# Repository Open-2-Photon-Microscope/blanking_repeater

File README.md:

# blanking_repeater
an electronic circuit to distribute blanking signal (or any type of ttl signal) to multiple outputs

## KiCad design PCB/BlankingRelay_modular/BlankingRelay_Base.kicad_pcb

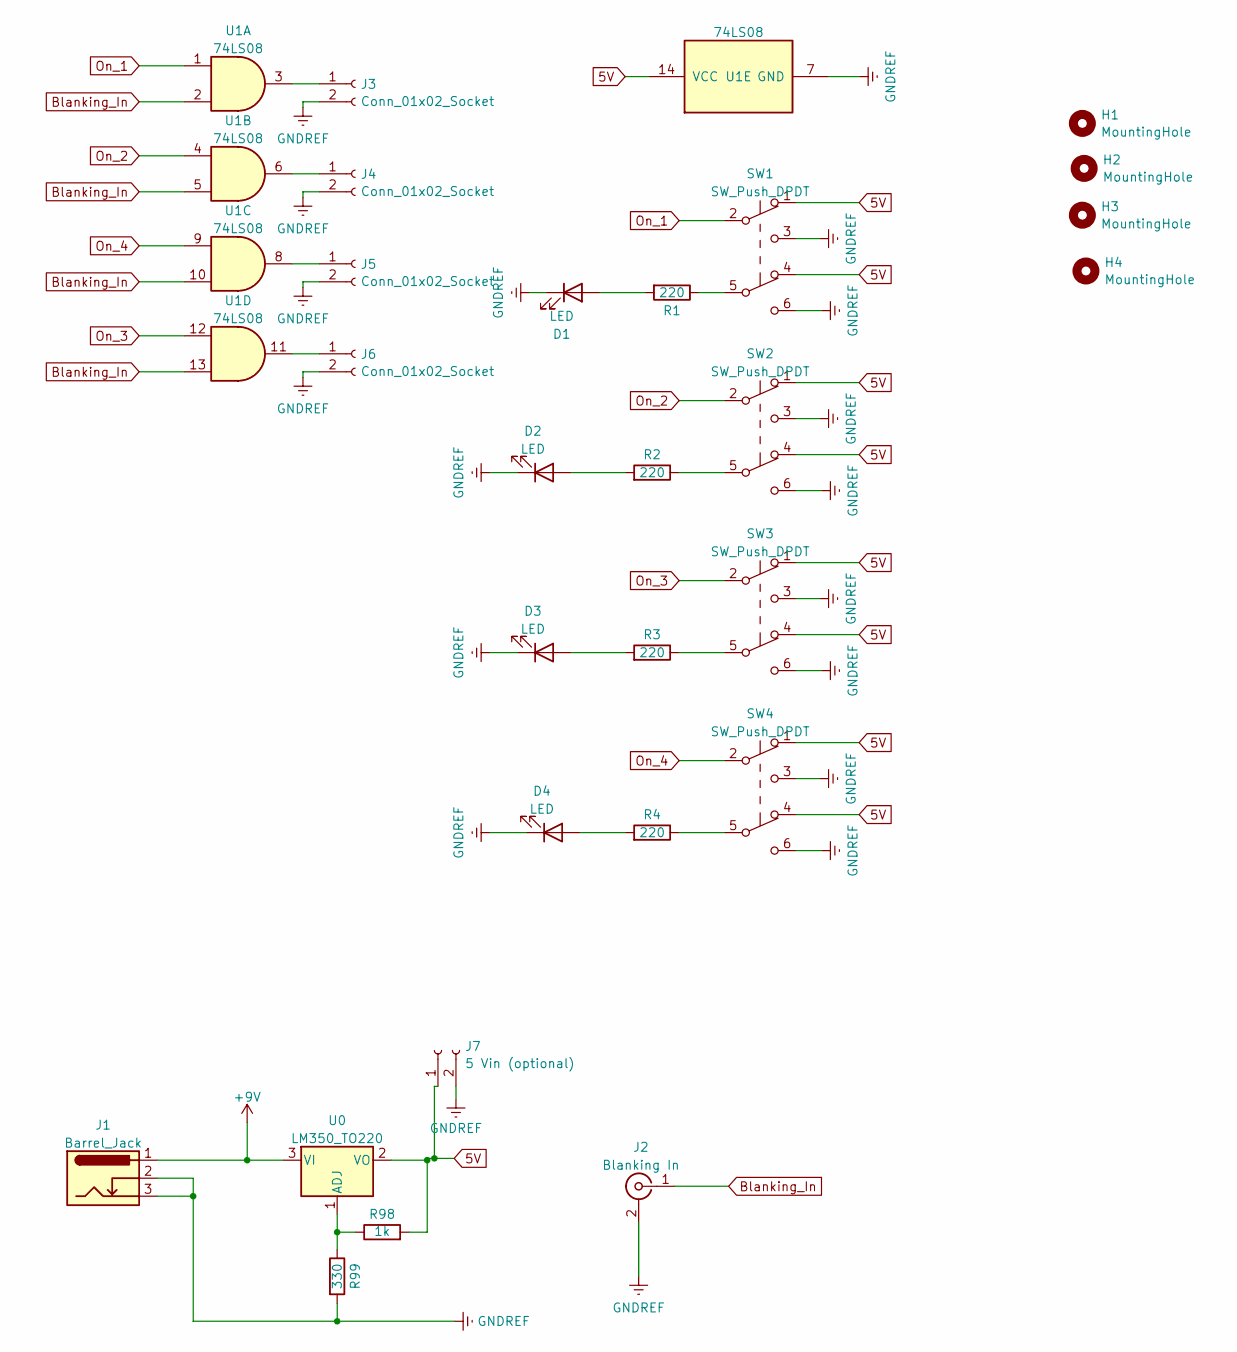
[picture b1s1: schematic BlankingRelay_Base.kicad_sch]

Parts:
D1, D2, D3, D4: LED; LED_D3.0mm
H1, H2, H3, H4: MountingHole; MountingHole_3.2mm_M3
J1: Barrel_Jack; BarrelJack_Horizontal
J2: Blanking In; BNC_Socket_TYCO-AMP_LargePads
J3, J4, J5, J6: Conn_01x02_Socket; JST_XH_B2B-XH-A_1x02_P2.50mm_Vertical
J7: 5 Vin (optional); JST_XH_B2B-XH-A_1x02_P2.50mm_Vertical
R1, R2, R3, R4: 220; R_Axial_DIN0309_L9.0mm_D3.2mm_P15.24mm_Horizontal
R98: 1k; R_Axial_DIN0309_L9.0mm_D3.2mm_P15.24mm_Horizontal
R99: 330; R_Axial_DIN0309_L9.0mm_D3.2mm_P15.24mm_Horizontal
SW1, SW2, SW3, SW4: SW_Push_DPDT; maxi_DPDT_Angled
U0: LM350_TO220; TO-220-3_Vertical
U1: 74LS08; DIP-14_W7.62mm_LongPads

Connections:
5V: J7.1, R98.2, SW1.1 (A), SW1.4 (A), SW2.1 (A), SW2.4 (A), SW3.1 (A), SW3.4 (A), SW4.1 (A), SW4.4 (A), U0.2 (VO), U1.14 (VCC); also elsewhere on the board
+9V: J1.1, U0.3 (VI)
Blanking_In: J2.1 (In), U1.2, U1.5, U1.10, U1.13
GNDREF: D1.1 (K), D2.1 (K), D3.1 (K), D4.1 (K), J1.2, J1.3, J2.2 (Ext), J3.2, J4.2, J5.2, J6.2, J7.2, R99.2, SW1.3 (C), SW1.6 (C), SW2.3 (C), SW2.6 (C), SW3.3 (C), SW3.6 (C), SW4.3 (C), SW4.6 (C), U1.7 (GND); also elsewhere on the board
unnamed: D1.2 (A), R1.2
unnamed: D2.2 (A), R2.2
unnamed: D3.2 (A), R3.2
unnamed: D4.2 (A), R4.2
unnamed: J3.1, U1.3
unnamed: J4.1, U1.6
unnamed: J5.1, U1.8
unnamed: J6.1, U1.11
unnamed: R1.1, SW1.5 (B)
unnamed: R2.1, SW2.5 (B)
unnamed: R3.1, SW3.5 (B)
unnamed: R4.1, SW4.5 (B)
unnamed 16: R98.1, R99.1, U0.1 (ADJ); also elsewhere on the board
On_1: SW1.2 (B), U1.1
On_2: SW2.2 (B), U1.4
On_3: SW3.2 (B), U1.12
On_4: SW4.2 (B), U1.9

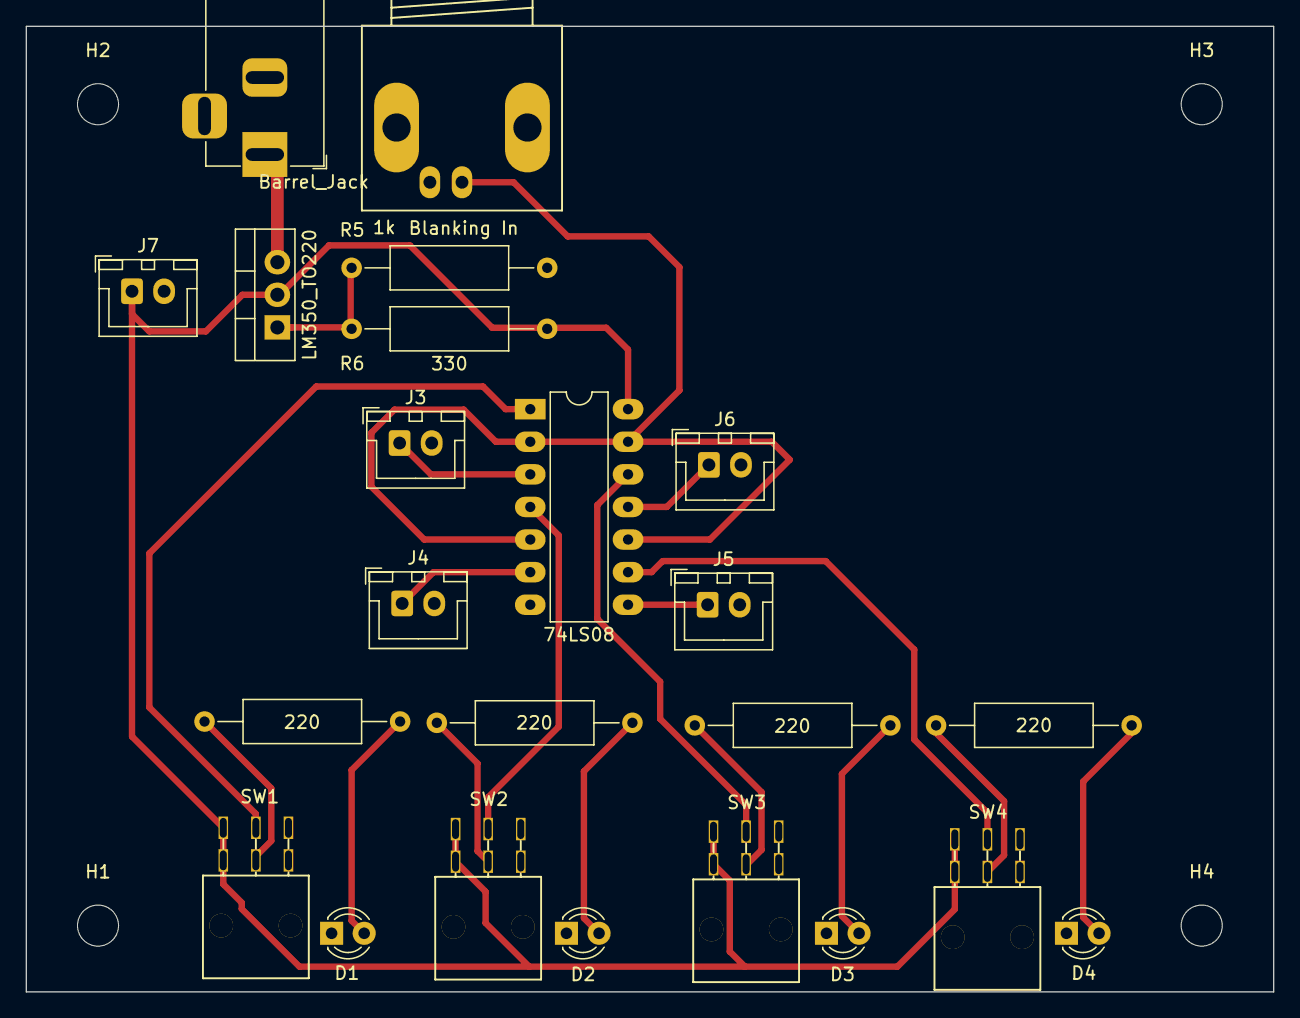
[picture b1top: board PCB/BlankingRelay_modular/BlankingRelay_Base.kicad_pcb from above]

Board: 2 copper layers, 97.2 x 75.2 mm, 27 parts (0 on the bottom side), 21 nets.

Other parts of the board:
R5: 1k; R_Axial_DIN0309_L9.0mm_D3.2mm_P15.24mm_Horizontal
R6: 330; R_Axial_DIN0309_L9.0mm_D3.2mm_P15.24mm_Horizontal

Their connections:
5V: R6.2; also elsewhere on the board
GNDREF: R5.2; also elsewhere on the board
unnamed 16: R5.1, R6.1; also elsewhere on the board

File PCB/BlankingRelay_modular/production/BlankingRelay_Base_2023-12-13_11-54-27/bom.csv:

Designator,Footprint,Quantity,Value,LCSC Part #
"D1, D2, D3, D4",LED_D3.0mm,4,LED,
"H1, H2, H3, H4",MountingHole_3.2mm_M3,4,MountingHole,
J1,BarrelJack_Horizontal,1,Barrel_Jack,
J2,BNC_Socket_TYCO-AMP_LargePads,1,Blanking In,
"J3, J4, J5, J6",JST_XH_B2B-XH-A_1x02_P2.50mm_Vertical,4,Conn_01x02_Socket,
J7,JST_XH_B2B-XH-A_1x02_P2.50mm_Vertical,1,5 Vin (optional),
"R1, R2, R3, R4",R_Axial_DIN0309_L9.0mm_D3.2mm_P15.24mm_Horizontal,4,220,
R98,R_Axial_DIN0309_L9.0mm_D3.2mm_P15.24mm_Horizontal,1,1k,
R99,R_Axial_DIN0309_L9.0mm_D3.2mm_P15.24mm_Horizontal,1,330,
"SW1, SW2, SW3, SW4",maxi_DPDT_Angled,4,SW_Push_DPDT,
U0,TO-220-3_Vertical,1,LM350_TO220,
U1,DIP-14_W7.62mm_LongPads,1,74LS08,

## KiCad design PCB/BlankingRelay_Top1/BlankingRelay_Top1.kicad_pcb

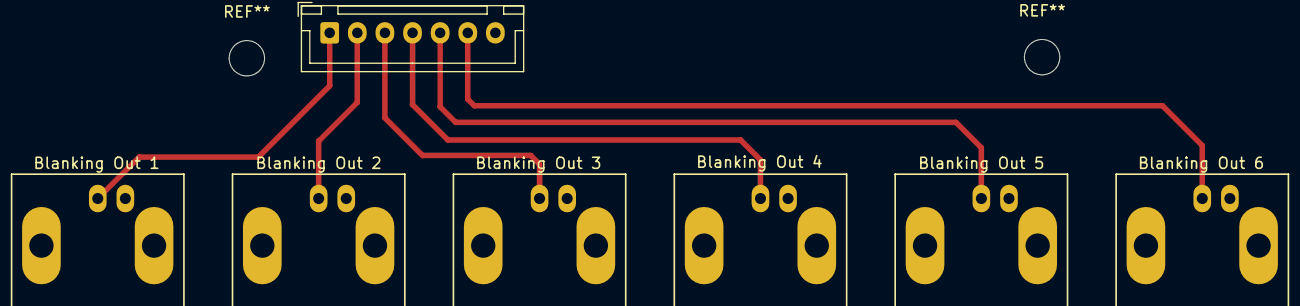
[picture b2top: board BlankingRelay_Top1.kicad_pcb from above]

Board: 2 copper layers, 7 parts (0 on the bottom side), 7 nets.

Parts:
J1: JST 7; JST_XH_B7B-XH-A_1x07_P2.50mm_Vertical
J2: Blanking Out 1; BNC_Socket_TYCO-AMP_LargePads
J3: Blanking Out 2; BNC_Socket_TYCO-AMP_LargePads
J4: Blanking Out 3; BNC_Socket_TYCO-AMP_LargePads
J5: Blanking Out 4; BNC_Socket_TYCO-AMP_LargePads
J6: Blanking Out 5; BNC_Socket_TYCO-AMP_LargePads
J7: Blanking Out 6; BNC_Socket_TYCO-AMP_LargePads

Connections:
Blanking_Out1: J1.1, J2.1 (In)
Blanking_Out2: J1.2, J3.1 (In)
Blanking_Out3: J1.3, J4.1 (In)
Blanking_Out4: J1.4, J5.1 (In)
Blanking_Out5: J1.5, J6.1 (In)
Blanking_Out6: J1.6, J7.1 (In)
GNDREF: J1.7, J2.2 (Ext), J3.2 (Ext), J4.2 (Ext), J5.2 (Ext), J6.2 (Ext), J7.2 (Ext)

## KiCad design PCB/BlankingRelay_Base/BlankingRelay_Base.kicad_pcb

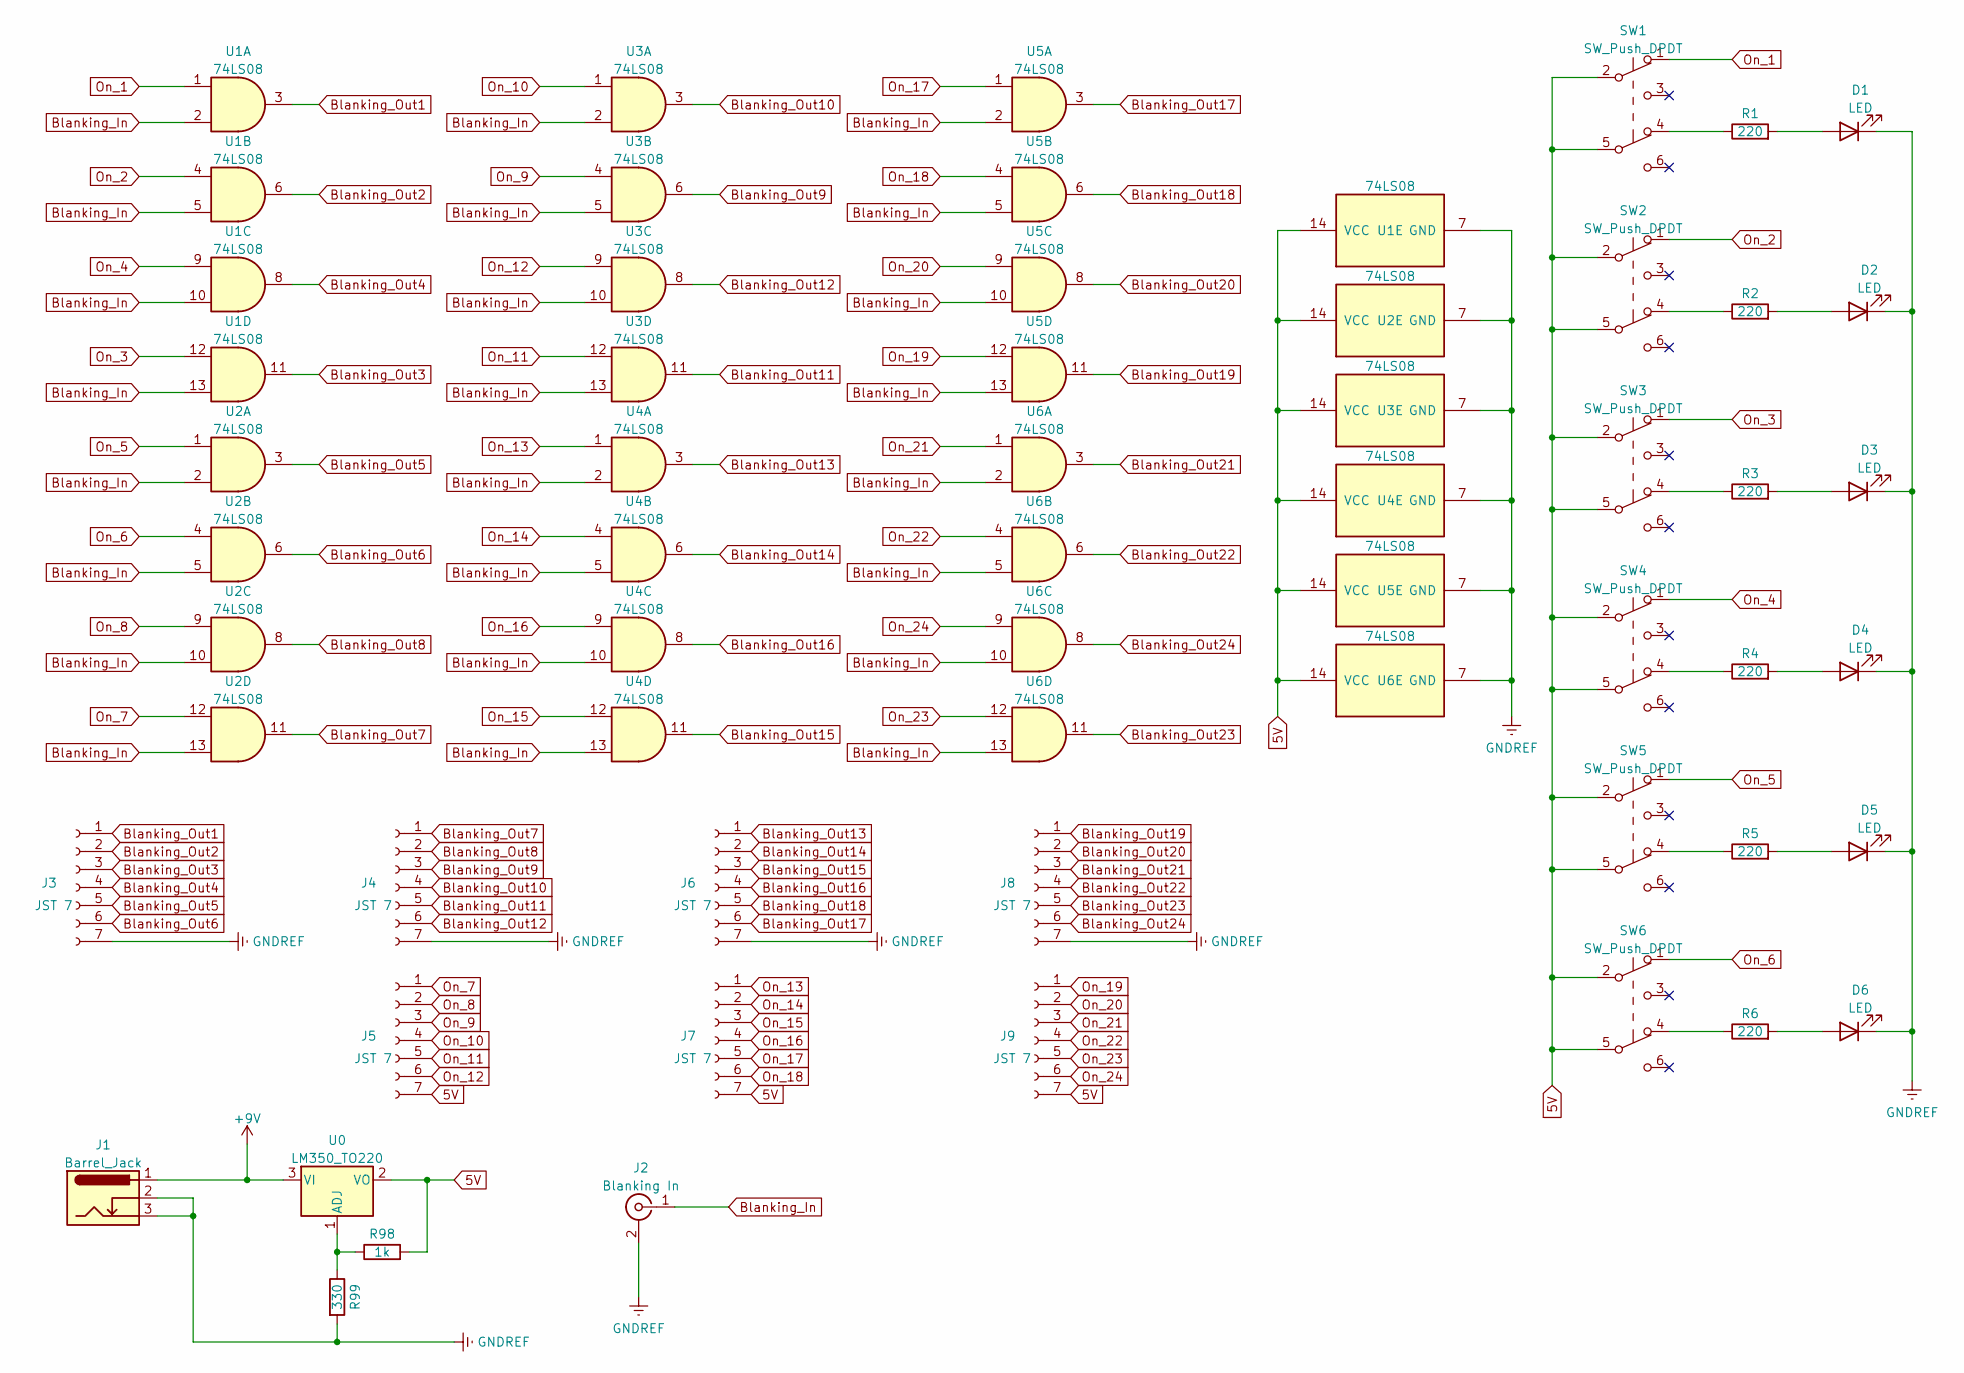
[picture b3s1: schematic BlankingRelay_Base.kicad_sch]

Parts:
D1, D2, D3, D4, D5, D6: LED; LED_D3.0mm
J1: Barrel_Jack; BarrelJack_Horizontal
J2: Blanking In; BNC_Socket_TYCO-AMP_LargePads
J3, J4, J5, J6, J7, J8, J9: JST 7; JST_XH_B7B-XH-A_1x07_P2.50mm_Vertical
R1, R2, R3, R4, R5, R6: 220; R_Axial_DIN0309_L9.0mm_D3.2mm_P15.24mm_Horizontal
R98: 1k; R_Axial_DIN0309_L9.0mm_D3.2mm_P15.24mm_Horizontal
R99: 330; R_Axial_DIN0309_L9.0mm_D3.2mm_P15.24mm_Horizontal
SW1, SW2, SW3, SW4, SW5, SW6: SW_Push_DPDT; maxi_DPDT_Angled
U0: LM350_TO220; TO-220-3_Vertical
U1, U2, U3, U4, U5, U6: 74LS08; DIP-14_W7.62mm_LongPads

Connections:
5V: J5.7, J7.7, J9.7, R98.2, SW1.2 (B), SW1.5 (B), SW2.2 (B), SW2.5 (B), SW3.2 (B), SW3.5 (B), SW4.2 (B), SW4.5 (B), SW5.2 (B), SW5.5 (B), SW6.2 (B), SW6.5 (B), U0.2 (VO), U1.14 (VCC), U2.14 (VCC), U3.14 (VCC), U4.14 (VCC), U5.14 (VCC), U6.14 (VCC)
+9V: J1.1, U0.3 (VI)
Blanking_In: J2.1 (In), U1.2, U1.5, U1.10, U1.13, U2.2, U2.5, U2.10, U2.13, U3.2, U3.5, U3.10, U3.13, U4.2, U4.5, U4.10, U4.13, U5.2, U5.5, U5.10, U5.13, U6.2, U6.5, U6.10, U6.13
Blanking_Out1: J3.1, U1.3
Blanking_Out2: J3.2, U1.6
Blanking_Out3: J3.3, U1.11
Blanking_Out4: J3.4, U1.8
Blanking_Out5: J3.5, U2.3
Blanking_Out6: J3.6, U2.6
Blanking_Out7: J4.1, U2.11
Blanking_Out8: J4.2, U2.8
Blanking_Out9: J4.3, U3.6
Blanking_Out10: J4.4, U3.3
Blanking_Out11: J4.5, U3.11
Blanking_Out12: J4.6, U3.8
Blanking_Out13: J6.1, U4.3
Blanking_Out14: J6.2, U4.6
Blanking_Out15: J6.3, U4.11
Blanking_Out16: J6.4, U4.8
Blanking_Out17: J6.6, U5.3
Blanking_Out18: J6.5, U5.6
Blanking_Out19: J8.1, U5.11
Blanking_Out20: J8.2, U5.8
Blanking_Out21: J8.3, U6.3
Blanking_Out22: J8.4, U6.6
Blanking_Out23: J8.5, U6.11
Blanking_Out24: J8.6, U6.8
GNDREF: D1.1 (K), D2.1 (K), D3.1 (K), D4.1 (K), D5.1 (K), D6.1 (K), J1.2, J1.3, J2.2 (Ext), J3.7, J4.7, J6.7, J8.7, R99.2, U1.7 (GND), U2.7 (GND), U3.7 (GND), U4.7 (GND), U5.7 (GND), U6.7 (GND)
unnamed: D1.2 (A), R1.2
unnamed: D2.2 (A), R2.2
unnamed: D3.2 (A), R3.2
unnamed: D4.2 (A), R4.2
unnamed: D5.2 (A), R5.2
unnamed: D6.2 (A), R6.2
unnamed: R98.1, R99.1, U0.1 (ADJ)
unnamed: R1.1, SW1.4 (A)
unnamed: R2.1, SW2.4 (A)
unnamed: R3.1, SW3.4 (A)
unnamed: R4.1, SW4.4 (A)
unnamed: R5.1, SW5.4 (A)
unnamed: R6.1, SW6.4 (A)
On_1: SW1.1 (A), U1.1
On_2: SW2.1 (A), U1.4
On_3: SW3.1 (A), U1.12
On_4: SW4.1 (A), U1.9
On_5: SW5.1 (A), U2.1
On_6: SW6.1 (A), U2.4
On_7: J5.1, U2.12
On_8: J5.2, U2.9
On_9: J5.3, U3.4
On_10: J5.4, U3.1
On_11: J5.5, U3.12
On_12: J5.6, U3.9
On_13: J7.1, U4.1
On_14: J7.2, U4.4
On_15: J7.3, U4.12
On_16: J7.4, U4.9
On_17: J7.5, U5.1
On_18: J7.6, U5.4
On_19: J9.1, U5.12
On_20: J9.2, U5.9
On_21: J9.3, U6.1
On_22: J9.4, U6.4
On_23: J9.5, U6.12
On_24: J9.6, U6.9

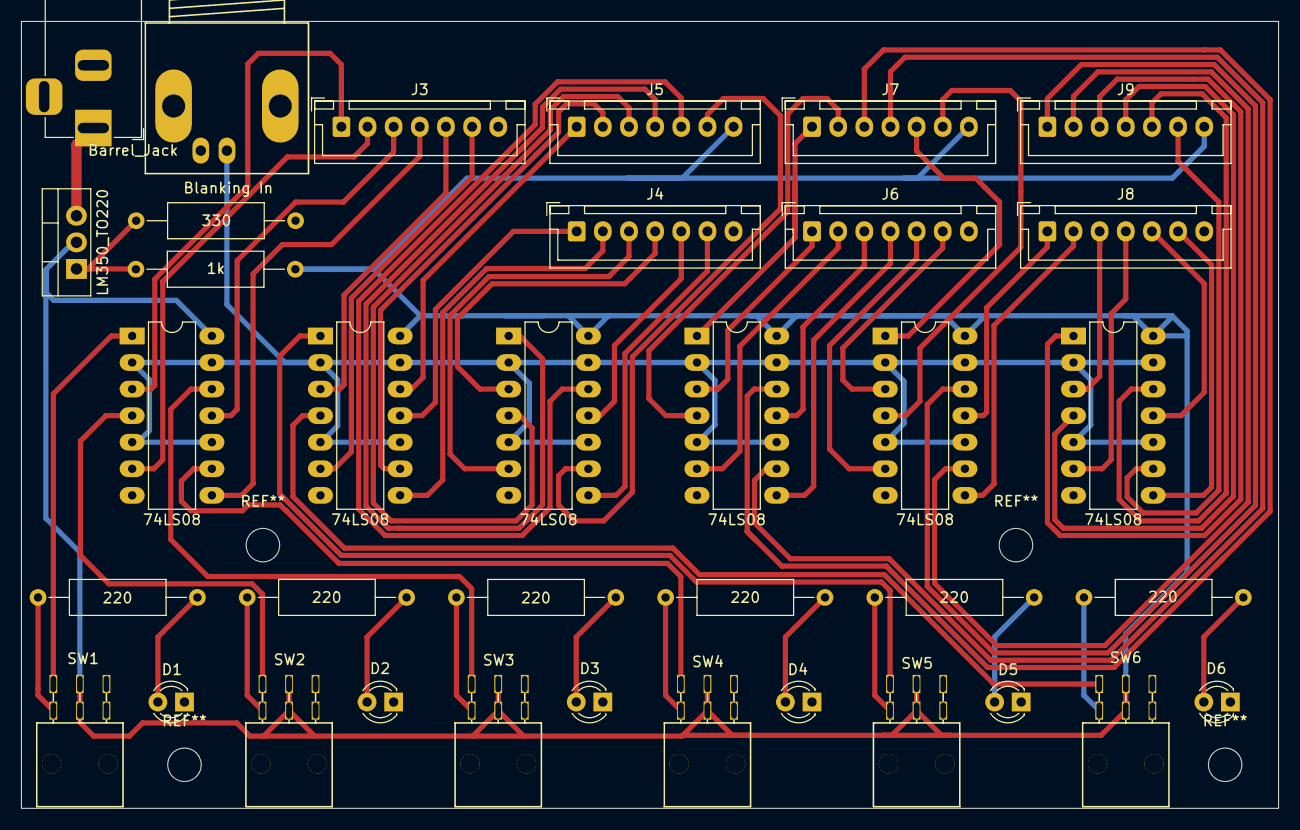
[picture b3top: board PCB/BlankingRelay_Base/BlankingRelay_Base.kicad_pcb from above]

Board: 2 copper layers, 120.2 x 75.2 mm, 36 parts (0 on the bottom side), 65 nets.

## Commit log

2023-12-05 first schematic design
2023-12-05 correct mistake
2023-12-05 add gitignore to make sure we are not uploading board backups
2023-12-08 First upload PCB for layer 1 and 2
2023-12-11 update base board to include outline and some keepout areas
2023-12-12 create a more modular board...
2023-12-13 remove autosave, make modular board ready for production
2024-01-05 minor bug correction
2024-01-05 minor bug corrections
2024-01-12 start enclosure
2024-02-16 update_enclosure
2024-02-19 update enclosure
2024-02-20 work_on enclosure 2
2024-02-20 fix enclosure2
